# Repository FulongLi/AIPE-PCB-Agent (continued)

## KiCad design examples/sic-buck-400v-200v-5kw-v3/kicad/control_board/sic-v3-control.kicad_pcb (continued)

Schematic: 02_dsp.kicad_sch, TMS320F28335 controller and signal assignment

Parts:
U5: TMS320F28335PGFA; LQFP-176_24x24mm_P0.5mm

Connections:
1V9: U5.4 (VDD), U5.15 (VDD), U5.23 (VDD), U5.29 (VDD), U5.31 (VDD1A18), U5.59 (VDD2A18), U5.61 (VDD), U5.101 (VDD), U5.109 (VDD), U5.117 (VDD), U5.126 (VDD), U5.139 (VDD), U5.146 (VDD), U5.154 (VDD), U5.167 (VDD); also elsewhere on the board
3V3: U5.9 (VDDIO), U5.34 (VDDA2), U5.45 (VDDAIO), U5.71 (VDDIO), U5.84 (VDD3VFL), U5.93 (VDDIO), U5.107 (VDDIO), U5.121 (VDDIO), U5.143 (VDDIO), U5.159 (VDDIO), U5.170 (VDDIO); also elsewhere on the board
ADCREFM: U5.55 (ADCREFM); also elsewhere on the board
ADCREFP: U5.56 (ADCREFP); also elsewhere on the board
ADCRESEXT: U5.57 (ADCRESEXT); also elsewhere on the board
ADC_BUS: U5.42 (ADCINA0); also elsewhere on the board
ADC_CURRENT: U5.41 (ADCINA1); also elsewhere on the board
ADC_IREF: U5.37 (ADCINA5); also elsewhere on the board
ADC_OUT: U5.39 (ADCINA3); also elsewhere on the board
ADC_RAW: U5.40 (ADCINA2); also elsewhere on the board
ADC_TEMP: U5.38 (ADCINA4); also elsewhere on the board
ADC_V12: U5.46 (ADCINB0); also elsewhere on the board
ARMED: U5.21 (GPIO12); also elsewhere on the board
ARM_PULSE: U5.7 (GPIO2); also elsewhere on the board
AUX_OK_N: U5.27 (GPIO16); also elsewhere on the board
BIAS_EN: U5.13 (GPIO6); also elsewhere on the board
BOOT84: U5.169 (GPIO84); also elsewhere on the board
BOOT85: U5.172 (GPIO85); also elsewhere on the board
BOOT86: U5.173 (GPIO86); also elsewhere on the board
BOOT87: U5.174 (GPIO87); also elsewhere on the board
CLK30: U5.105 (XCLKIN); also elsewhere on the board
CURRENT_OK: U5.24 (GPIO13); also elsewhere on the board
DRV_RESET: U5.12 (GPIO5); also elsewhere on the board
EMU0: U5.85 (EMU0); also elsewhere on the board
EMU1: U5.86 (EMU1); also elsewhere on the board
EPWM_A: U5.5 (GPIO0); also elsewhere on the board
EPWM_B: U5.6 (GPIO1); also elsewhere on the board
FAN_TACH: U5.68 (GPIO24); also elsewhere on the board
FLT_H_N: U5.16 (GPIO7); also elsewhere on the board
FLT_L_N: U5.17 (GPIO8); also elsewhere on the board
GND_CTRL: U5.3 (VSS), U5.8 (VSS), U5.14 (VSS), U5.22 (VSS), U5.30 (VSS), U5.32 (VSS1AGND), U5.33 (VSSA2), U5.35 (ADCINA7), U5.36 (ADCINA6), U5.43 (ADCLO), U5.44 (VSSAIO), U5.47 (ADCINB1), U5.48 (ADCINB2), U5.49 (ADCINB3), U5.50 (ADCINB4), U5.51 (ADCINB5), U5.52 (ADCINB6), U5.53 (ADCINB7), U5.54 (ADCREFIN), U5.58 (VSS2AGND), U5.60 (VSS), U5.70 (VSS), U5.83 (VSS), U5.92 (VSS), U5.103 (VSS), U5.104 (X1), U5.106 (VSS), U5.108 (VSS), U5.118 (VSS), U5.120 (VSS), U5.125 (VSS), U5.140 (VSS), U5.144 (VSS), U5.147 (VSS), U5.155 (VSS), U5.160 (VSS), U5.166 (VSS), U5.171 (VSS); also elsewhere on the board
MAIN_CMD: U5.10 (GPIO3); also elsewhere on the board
MAIN_FB: U5.64 (GPIO20); also elsewhere on the board
PG_H_N: U5.28 (GPIO17); also elsewhere on the board
PG_L_N: U5.62 (GPIO18); also elsewhere on the board
PG_S_N: U5.63 (GPIO19); also elsewhere on the board
PRE_CMD: U5.11 (GPIO4); also elsewhere on the board
PRE_FB: U5.65 (GPIO21); also elsewhere on the board
RDY_H: U5.18 (GPIO9); also elsewhere on the board
RDY_L: U5.19 (GPIO10); also elsewhere on the board
RUN_ENABLE: U5.20 (GPIO11); also elsewhere on the board
TCK: U5.87 (TCK); also elsewhere on the board
TDI: U5.76 (TDI); also elsewhere on the board
TDO: U5.77 (TDO); also elsewhere on the board
THERM_OK: U5.26 (GPIO15); also elsewhere on the board
TH_H_PWM: U5.69 (GPIO25); also elsewhere on the board
TH_L_PWM: U5.72 (GPIO26); also elsewhere on the board
TMS: U5.79 (TMS); also elsewhere on the board
TRST: U5.78 (TRST); also elsewhere on the board
UART_RX: U5.141 (GPIO28); also elsewhere on the board
UART_TX: U5.2 (GPIO29); also elsewhere on the board
VOLTAGE_OK: U5.25 (GPIO14); also elsewhere on the board
XRS_N: U5.80 (XRS); also elsewhere on the board

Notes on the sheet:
TMS320F28335 controller and signal assignment
TMS320F28335; ePWM dead-band + asynchronous TZ inputs

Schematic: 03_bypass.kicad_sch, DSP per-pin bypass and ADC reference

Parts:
C17, C18, C19, C20, C21, C22, C23, C24, C25, C26, C27, C28, C29, C30, C31, C32, C33, C34, C35, C36, C37, C38, C39, C40, C41, C42: 100n/50V; C_0603_1608Metric
C43, C44, C45, C46, C47, C48: 2.2u/25V; C_0805_2012Metric
R23: 22k; R_0603_1608Metric

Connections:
1V9: C17.1, C19.1, C20.1, C21.1, C22.1, C25.1, C26.1, C30.1, C32.1, C33.1, C35.1, C36.1, C38.1, C39.1, C41.1, C43.1, C44.1; also elsewhere on the board
3V3: C18.1, C23.1, C24.1, C27.1, C28.1, C29.1, C31.1, C34.1, C37.1, C40.1, C42.1, C45.1, C46.1; also elsewhere on the board
ADCREFM: C47.1; also elsewhere on the board
ADCREFP: C48.1; also elsewhere on the board
ADCRESEXT: R23.1; also elsewhere on the board
GND_CTRL: C17.2, C18.2, C19.2, C20.2, C21.2, C22.2, C23.2, C24.2, C25.2, C26.2, C27.2, C28.2, C29.2, C30.2, C31.2, C32.2, C33.2, C34.2, C35.2, C36.2, C37.2, C38.2, C39.2, C40.2, C41.2, C42.2, C43.2, C44.2, C45.2, C46.2, C47.2, C48.2, R23.2; also elsewhere on the board

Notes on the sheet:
DSP per-pin bypass and ADC reference
Per-pin capacitors; placement tied to actual DSP supply-pad positions

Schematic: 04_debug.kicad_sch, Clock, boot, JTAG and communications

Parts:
C49: 100n/50V; C_0603_1608Metric
J3: TI 14-pin JTAG; pin6 key; PinHeader_2x07_P2.54mm_Vertical
J4: 3.3 V UART; external cable length <=100 mm; PinHeader_1x04_P2.54mm_Vertical
R24: 33; R_0603_1608Metric
R25, R26, R27, R28, R29, R30, R31, R32, R34: 10k; R_0603_1608Metric
R33: 2.2k; R_0603_1608Metric
Y1: ASV-30.000MHZ-EJ-T; Oscillator_SMD_SeikoEpson_SG8002CA-4Pin_7.0x5.0mm

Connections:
3V3: C49.1, J3.5, J4.1, R25.1, R26.1, R27.1, R28.1, R29.1, R30.1, R31.1, R32.1, R34.1, Y1.1 (TRI), Y1.4 (VDD); also elsewhere on the board
BOOT84: R25.2; also elsewhere on the board
BOOT85: R26.2; also elsewhere on the board
BOOT86: R27.2; also elsewhere on the board
BOOT87: R28.2; also elsewhere on the board
CLK30: R24.2; also elsewhere on the board
CLK_SRC: R24.1, Y1.3 (OUT)
EMU0: J3.13, R31.2; also elsewhere on the board
EMU1: J3.14, R32.2; also elsewhere on the board
GND_CTRL: C49.2, J3.4, J3.8, J3.10, J3.12, J4.4, R33.2, Y1.2 (GND); also elsewhere on the board
TCK: J3.9, J3.11; also elsewhere on the board
TDI: J3.3, R30.2; also elsewhere on the board
TDO: J3.7; also elsewhere on the board
TMS: J3.1, R29.2; also elsewhere on the board
TRST: J3.2, R33.1; also elsewhere on the board
UART_RX: J4.3, R34.2; also elsewhere on the board
UART_TX: J4.2; also elsewhere on the board

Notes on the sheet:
Clock, boot, JTAG and communications
30 MHz clock and boot straps
JTAG and 3.3 V UART; accessible control domain only

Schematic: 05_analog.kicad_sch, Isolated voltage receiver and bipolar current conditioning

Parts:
C50, C51, C52, C53, C54, C55, C63, C64: 100p/50V; C_0603_1608Metric
C56, C60, C62, C65, C73: 100n/50V; C_0603_1608Metric
C57, C58, C59, C61: 1u/50V; C_0805_2012Metric
C66, C67, C68, C69, C70, C71, C72: 1n/50V; C_0603_1608Metric
D3, D4, D5, D6, D7, D8, D9, D10, D11, D12, D13, D14, D15, D16: BAT46W-E3-08; D_SOD-123
J5: LEM HO 50-S-0100; JST_PH_B5B-PH-K_1x05_P2.00mm_Vertical
R35, R37, R39, R41, R43, R45, R47, R48, R49, R51, R54, R65: 10k; R_0603_1608Metric
R36, R38, R40, R42, R44, R46: 15k; R_0603_1608Metric
R50, R52: 20k; R_0603_1608Metric
R53: 3.3k; R_0603_1608Metric
R55, R56: 1M; R_0603_1608Metric
R57, R58, R59, R60, R61, R62, R63: 220; R_0603_1608Metric
R64: 43k; R_0603_1608Metric
U6: OPA4192IPWR; TSSOP-14_4.4x5mm_P0.65mm
U7: REF3130AIDBZR; SOT-23
U8: OPA2320AIDGKR; V3_DGK8
U9: LM61CIM3/NOPB; SOT-23

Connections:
3V3: C73.1, D3.1 (K), D5.1 (K), D7.1 (K), D9.1 (K), D11.1 (K), D13.1 (K), D15.1 (K), U9.1 (+VS); also elsewhere on the board
5V: C56.1, C57.1, C58.1, C61.1, C62.1, C65.1, J5.1, U6.4 (V+), U7.1 (IN), U8.8 (V+); also elsewhere on the board
12V_E: R64.1; also elsewhere on the board
ADC_BUS: C66.1, D3.2 (A), D4.1 (K), R57.2; also elsewhere on the board
ADC_CURRENT: C69.1, D9.2 (A), D10.1 (K), R60.2; also elsewhere on the board
ADC_IREF: C70.1, D11.2 (A), D12.1 (K), R61.2; also elsewhere on the board
ADC_OUT: C68.1, D7.2 (A), D8.1 (K), R59.2; also elsewhere on the board
ADC_RAW: C67.1, D5.2 (A), D6.1 (K), R58.2; also elsewhere on the board
ADC_TEMP: C71.1, D13.2 (A), D14.1 (K), R62.2; also elsewhere on the board
ADC_V12: C72.1, D15.2 (A), D16.1 (K), R63.2; also elsewhere on the board
BUS_A: C53.1, R41.2, R42.1, U6.5 (+)
BUS_M: C52.2, R39.2, R40.2, U6.6 (-)
BUS_N: R39.1; also elsewhere on the board
BUS_P: R41.1; also elsewhere on the board
BUS_V: C52.1, R40.1, R57.1, U6.7 (OUTB); also elsewhere on the board
GND_CTRL: C51.2, C53.2, C55.2, C56.2, C57.2, C58.2, C59.2, C60.2, C61.2, C62.2, C65.2, C66.2, C67.2, C68.2, C69.2, C70.2, C71.2, C72.2, C73.2, D4.2 (A), D6.2 (A), D8.2 (A), D10.2 (A), D12.2 (A), D14.2 (A), D16.2 (A), J5.2, R38.2, R42.2, R46.2, R48.2, R54.2, R55.2, R56.2, R65.2, U6.11 (V-), U7.3 (GND), U8.4 (V-), U9.3 (GND); also elsewhere on the board
I_A: C64.1, R51.2, R52.2, U8.5 (+)
I_M: C63.2, R49.2, R50.2, U8.6 (-)
I_OCD_N: R53.2, R54.1; also elsewhere on the board
I_OCD_RAW: J5.5, R53.1
I_RAW: J5.3, R51.1, R55.1
I_REF: J5.4, R56.1, U8.3 (+)
I_REF_BUF: R49.1, R61.1, U8.1 (OUTA), U8.2 (-)
I_V: C63.1, R50.1, R60.1, U8.7 (OUTB); also elsewhere on the board
MID1V5: C64.2, R52.1, U6.13 (-), U6.14 (OUTD)
MID_DIV: C60.1, R47.2, R48.1, U6.12 (+)
OUT_A: C55.1, R45.2, R46.1, U6.10 (+)
OUT_M: C54.2, R43.2, R44.2, U6.9 (-)
OUT_N: R43.1; also elsewhere on the board
OUT_P: R45.1; also elsewhere on the board
OUT_V: C54.1, R44.1, R59.1, U6.8 (OUTC); also elsewhere on the board
RAW_A: C51.1, R37.2, R38.1, U6.3 (+)
RAW_M: C50.2, R35.2, R36.2, U6.2 (-)
RAW_N: R35.1; also elsewhere on the board
RAW_P: R37.1; also elsewhere on the board
RAW_V: C50.1, R36.1, R58.1, U6.1 (OUTA); also elsewhere on the board
REF3: C59.1, R47.1, U7.2 (OUT); also elsewhere on the board
TEMP_V: R62.1, U9.2 (VOUT)
V12_DIV: R63.1, R64.2, R65.1

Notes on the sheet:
Isolated voltage receiver and bipolar current conditioning
Balanced differential voltage receivers; output = 1.5 x differential input
Bipolar current measurement; buffered actual sensor reference
ADC charge reservoirs and input protection

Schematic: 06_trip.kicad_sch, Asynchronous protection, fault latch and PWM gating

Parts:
C74, C75, C76, C77, C78, C79, C80, C81, C82, C83, C84, C85, C86, C87, C88: 100n/50V; C_0603_1608Metric
D17, D18, D19, D20, D21, D22, D23, D24: BAT46W-E3-08; D_SOD-123
R66, R69: 90.9k; R_0603_1608Metric
R67, R68: 9.53k; R_0603_1608Metric
R70: 34k; R_0603_1608Metric
R71, R73, R75: 100k; R_0603_1608Metric
R72: 77k; R_0603_1608Metric
R74: 33.2k; R_0603_1608Metric
R76, R77, R78, R79: 1k; R_0603_1608Metric
R80, R81, R82, R83, R84, R85: 10k; R_0603_1608Metric
R86, R87: 33; R_0603_1608Metric
TP2: TRIPPED; TestPoint_Pad_D1.0mm
TP3: ALL_GOOD; TestPoint_Pad_D1.0mm
U10, U11, U12: TLV3202AIDGKR; V3_DGK8
U13: SN74LV04APWR; TSSOP-14_4.4x5mm_P0.65mm
U14, U15, U16: SN74LV21APWR; TSSOP-14_4.4x5mm_P0.65mm
U17, U19: SN74LVC2G08DCTR; SSOP-8_2.95x2.8mm_P0.65mm
U18: SN74LVC1G74DCTR; SSOP-8_2.95x2.8mm_P0.65mm

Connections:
3V3: C79.1, C80.1, C81.1, C82.1, C83.1, C84.1, C85.1, C86.1, C87.1, C88.1, D17.1 (K), D19.1 (K), D21.1 (K), D23.1 (K), U10.8 (V+), U11.8 (V+), U12.8 (V+), U13.14 (VCC), U14.5 (1D), U14.14 (VCC), U15.14 (VCC), U16.12 (2C), U16.13 (2D), U16.14 (VCC), U17.8 (VCC), U18.2 (D), U18.7 (PRE_N), U18.8 (VCC), U19.8 (VCC); also elsewhere on the board
ALL_GOOD: TP3.1, U17.7 (1Y), U18.6 (CLR_N)
ARMED: U17.5 (2A), U18.5 (Q); also elsewhere on the board
ARM_PULSE: R81.1, U18.1 (CLK); also elsewhere on the board
AUX_OK_N: U15.13 (2D); also elsewhere on the board
BIAS_EN: R85.1; also elsewhere on the board
BIAS_OK: U15.8 (2Y), U16.5 (1D)
BUS_CMP: D19.2 (A), D20.1 (K), R77.2, U11.3 (+), U12.2 (-)
BUS_OV_OK: U12.1 (OUTA), U14.12 (2C)
BUS_V: R77.1; also elsewhere on the board
COIL_INHIBIT: U13.8 (4Y); also elsewhere on the board
CURRENT_OK: U14.6 (1Y), U16.1 (1A); also elsewhere on the board
DRIVERS_OK: U15.6 (1Y), U16.4 (1C)
DRV_RESET: R84.1; also elsewhere on the board
EPWM_A: R82.1, U19.1 (1A); also elsewhere on the board
EPWM_B: R83.1, U19.5 (2A); also elsewhere on the board
FLT_H_N: U15.1 (1A); also elsewhere on the board
FLT_L_N: U15.2 (1B); also elsewhere on the board
GND_CTRL: C74.2, C75.2, C76.2, C77.2, C78.2, C79.2, C80.2, C81.2, C82.2, C83.2, C84.2, C85.2, C86.2, C87.2, C88.2, D18.2 (A), D20.2 (A), D22.2 (A), D24.2 (A), R67.2, R69.2, R71.2, R73.2, R75.2, R80.2, R81.2, R82.2, R83.2, R84.2, R85.2, U10.4 (V-), U11.4 (V-), U12.4 (V-), U13.7 (GND), U13.11 (5A), U13.13 (6A), U14.7 (GND), U15.7 (GND), U16.7 (GND), U17.4 (GND), U18.4 (GND), U19.4 (GND); also elsewhere on the board
I_CMP: D17.2 (A), D18.1 (K), R76.2, U10.3 (+), U10.6 (-)
I_HI: C75.1, R68.2, R69.1, U10.5 (+)
I_HIGH_OK: U10.7 (OUTB), U14.2 (1B)
I_LO: C74.1, R66.2, R67.1, U10.2 (-)
I_LOW_OK: U10.1 (OUTA), U14.1 (1A)
I_OCD_N: U14.4 (1C); also elsewhere on the board
I_V: R76.1; also elsewhere on the board
OUT_CMP: D23.2 (A), D24.1 (K), R79.2, U11.6 (-)
OUT_V: R79.1; also elsewhere on the board
PG_H_N: U13.1 (1A); also elsewhere on the board
PG_H_OK: U13.2 (1Y), U15.9 (2A)
PG_L_N: U13.3 (2A); also elsewhere on the board
PG_L_OK: U13.4 (2Y), U15.10 (2B)
PG_S_N: U13.5 (3A); also elsewhere on the board
PG_S_OK: U13.6 (3Y), U15.12 (2C)
PWM_ENABLE: U17.3 (2Y), U19.2 (1B), U19.6 (2B)
PWM_H: R86.2; also elsewhere on the board
PWM_H_SRC: R86.1, U19.7 (1Y)
PWM_L: R87.2; also elsewhere on the board
PWM_L_SRC: R87.1, U19.3 (2Y)
RAW_CMP: D21.2 (A), D22.1 (K), R78.2, U12.6 (-)
RAW_OV_OK: U12.7 (OUTB), U14.13 (2D)
RAW_V: R78.1; also elsewhere on the board
RDY_H: U15.4 (1C); also elsewhere on the board
RDY_L: U15.5 (1D); also elsewhere on the board
REF3: R66.1, R68.1, R70.1, R72.1, R74.1; also elsewhere on the board
RUN_ENABLE: R80.1, U17.6 (2B); also elsewhere on the board
STAGE_OK: U16.6 (1Y), U17.1 (1A)
SYSTEM_OK: U13.9 (4A), U16.8 (2Y), U17.2 (1B)
THERM_OK: U16.9 (2A); also elsewhere on the board
TRIPPED: TP2.1, U18.3 (Q_N)
VOLTAGE_OK: U14.8 (2Y), U16.2 (1B); also elsewhere on the board
V_BUSOV: C78.1, R74.2, R75.1, U12.3 (+), U12.5 (+)
V_HIGH_OK: U11.7 (OUTB), U14.10 (2B)
V_LOW_OK: U11.1 (OUTA), U14.9 (2A)
V_OV: C76.1, R70.2, R71.1, U11.5 (+)
V_UV: C77.1, R72.2, R73.1, U11.2 (-)
XRS_N: U16.10 (2B); also elsewhere on the board

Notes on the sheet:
Asynchronous protection, fault latch and PWM gating
Hardware current window ±38 A, OVP225 V and UVLO340 V
Power-good polarity, asynchronous fault tree and latched inhibit

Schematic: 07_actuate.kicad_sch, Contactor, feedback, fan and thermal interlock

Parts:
C89: 100u/25V; CP_Elec_8x10.5
C90: 100n/50V; C_0603_1608Metric
C91, C92: 10n/50V; C_0603_1608Metric
D25, D26: SSC54-E3/57T; D_SMC
J6: 12 V COIL / FAN; TerminalBlock_Phoenix_MKDS-1,5-2-5.08_1x02_P5.08mm_Horizont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
J7: MAIN COIL; TerminalBlock_Phoenix_MKDS-1,5-2-5.08_1x02_P5.08mm_Horizont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
J8: PRE COIL; TerminalBlock_Phoenix_MKDS-1,5-2-5.08_1x02_P5.08mm_Horizont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
J9: MAIN AUX CONTACT; PinHeader_1x02_P2.54mm_Vertical
J10: PRE AUX CONTACT; PinHeader_1x02_P2.54mm_Vertical
J11: Series NC90C sink thermostat + NC110C choke therm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; PinHeader_1x02_P2.54mm_Vertical
J12: 12V fan; open-collector tach; fan failure checked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; PinHeader_1x03_P2.54mm_Vertical
Q2, Q3: IRLZ44NPBF; TO-220-3_Vertical
R88, R90: 100; R_0603_1608Metric
R89, R91, R92, R93, R97, R101: 10k; R_0603_1608Metric
R94, R95, R98, R99: 200; R_2512_6332Metric
R96, R100: 33k; R_0603_1608Metric
R102: 1k; R_0603_1608Metric
R103: 4.7k; R_0603_1608Metric
U20: SN74AHCT125PWR; TSSOP-14_4.4x5mm_P0.65mm

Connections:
3V3: J11.1, R103.1; also elsewhere on the board
5V: C90.1, U20.10 (3OE_N), U20.13 (4OE_N), U20.14 (VCC); also elsewhere on the board
12V_COIL: C89.1, D25.1 (K), D26.1 (K), J6.1, J7.1, J8.1, J9.1, J10.1, J12.2
COIL_INHIBIT: U20.1 (1OE_N), U20.4 (2OE_N); also elsewhere on the board
FAN_TACH: J12.3, R103.2; also elsewhere on the board
GND_CTRL: C89.2, C90.2, C91.2, C92.2, J6.2, J12.1, Q2.3 (S), Q3.3 (S), R89.2, R91.2, R92.2, R93.2, R94.2, R95.2, R97.2, R98.2, R99.2, R101.2, R102.2, U20.7 (GND), U20.9 (3A), U20.12 (4A); also elsewhere on the board
MAIN_AUX: J9.2, R94.1, R95.1, R96.1
MAIN_CMD: R92.1, U20.2 (1A); also elsewhere on the board
MAIN_DRIVE: R88.1, U20.3 (1Y)
MAIN_FB: C91.1, R96.2, R97.1; also elsewhere on the board
MAIN_G: Q2.1 (G), R88.2, R89.1
MAIN_LOW: D25.2 (A), J7.2, Q2.2 (D)
PRE_AUX: J10.2, R98.1, R99.1, R100.1
PRE_CMD: R93.1, U20.5 (2A); also elsewhere on the board
PRE_DRIVE: R90.1, U20.6 (2Y)
PRE_FB: C92.1, R100.2, R101.1; also elsewhere on the board
PRE_G: Q3.1 (G), R90.2, R91.1
PRE_LOW: D26.2 (A), J8.2, Q3.2 (D)
THERM_OK: J11.2, R102.1; also elsewhere on the board

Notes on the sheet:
Contactor, feedback, fan and thermal interlock
Dedicated 12 V coil/fan branch; external 8 A fuse and return
Main and precharge drivers; fail-safe default off
Contactor auxiliary contacts with manufacturer minimum wetting current
Fail-open thermal / emergency-stop loop and fan tachometer

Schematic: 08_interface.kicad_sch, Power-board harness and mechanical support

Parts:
H1, H2, H3, H4: M3 insulated standoff; MountingHole_3.2mm_M3
J13: POWER / CONTROL — 40-way; IDC-Header_2x20_P2.54mm_Vertical

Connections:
3V3: J13.37, J13.38; also elsewhere on the board
12V_E: J13.33, J13.34; also elsewhere on the board
BIAS_EN: J13.8; also elsewhere on the board
BUS_N: J13.26; also elsewhere on the board
BUS_P: J13.25; also elsewhere on the board
DRV_RESET: J13.6; also elsewhere on the board
FLT_H_N: J13.10; also elsewhere on the board
FLT_L_N: J13.12; also elsewhere on the board
GND_CTRL: J13.1, J13.3, J13.5, J13.7, J13.9, J13.11, J13.13, J13.15, J13.17, J13.19, J13.21, J13.29, J13.31, J13.35, J13.36, J13.39, J13.40; also elsewhere on the board
OUT_N: J13.28; also elsewhere on the board
OUT_P: J13.27; also elsewhere on the board
PG_H_N: J13.18; also elsewhere on the board
PG_L_N: J13.20; also elsewhere on the board
PG_S_N: J13.22; also elsewhere on the board
PWM_H: J13.2; also elsewhere on the board
PWM_L: J13.4; also elsewhere on the board
RAW_N: J13.24; also elsewhere on the board
RAW_P: J13.23; also elsewhere on the board
RDY_H: J13.14; also elsewhere on the board
RDY_L: J13.16; also elsewhere on the board
TH_H_PWM: J13.30; also elsewhere on the board
TH_L_PWM: J13.32; also elsewhere on the board

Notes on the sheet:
Power-board harness and mechanical support
Keyed SELV harness to the power board
Mechanical

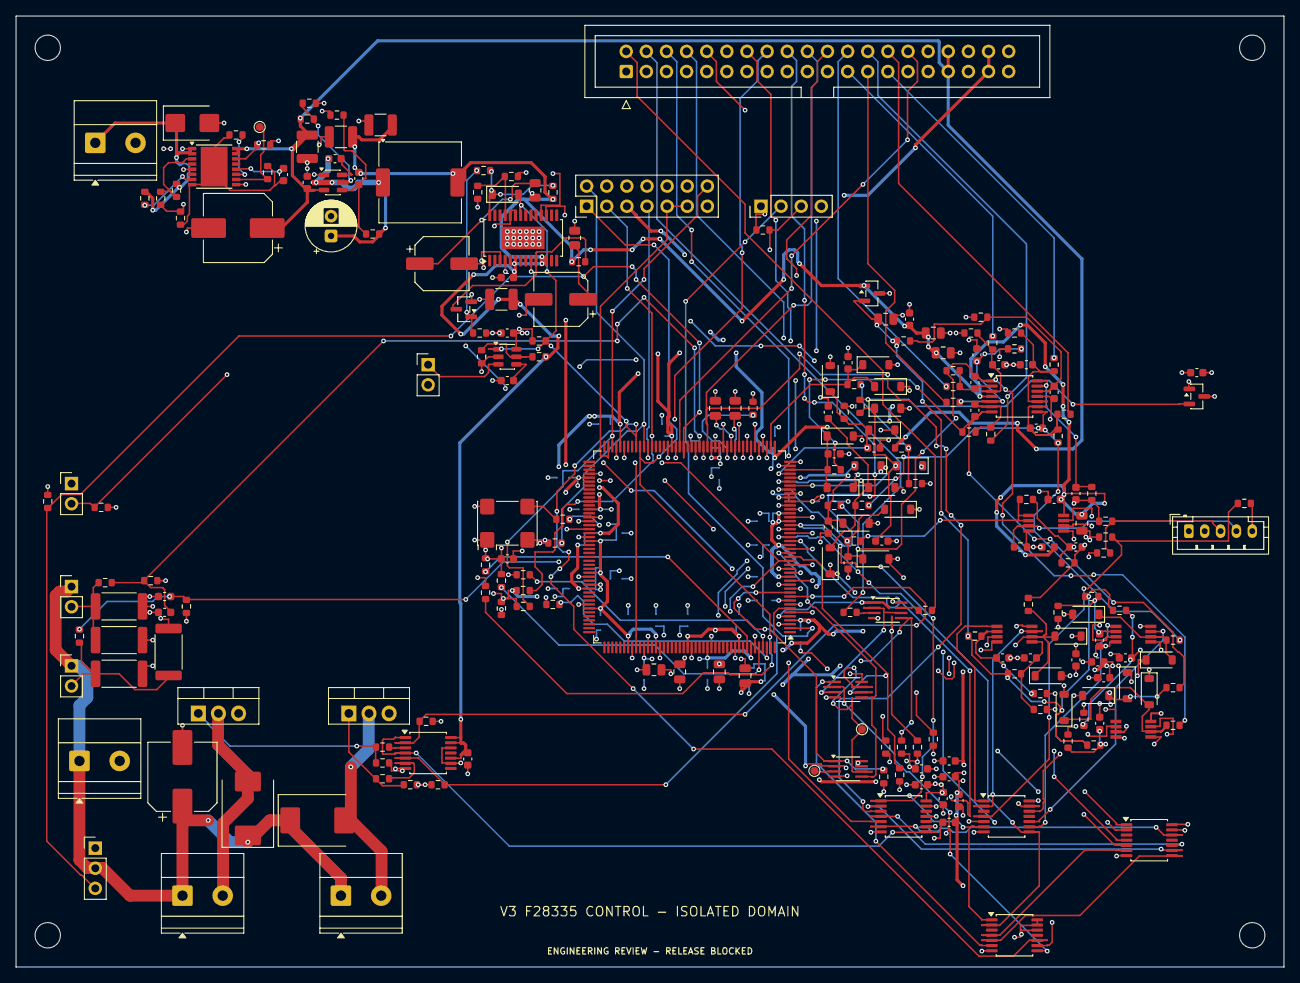
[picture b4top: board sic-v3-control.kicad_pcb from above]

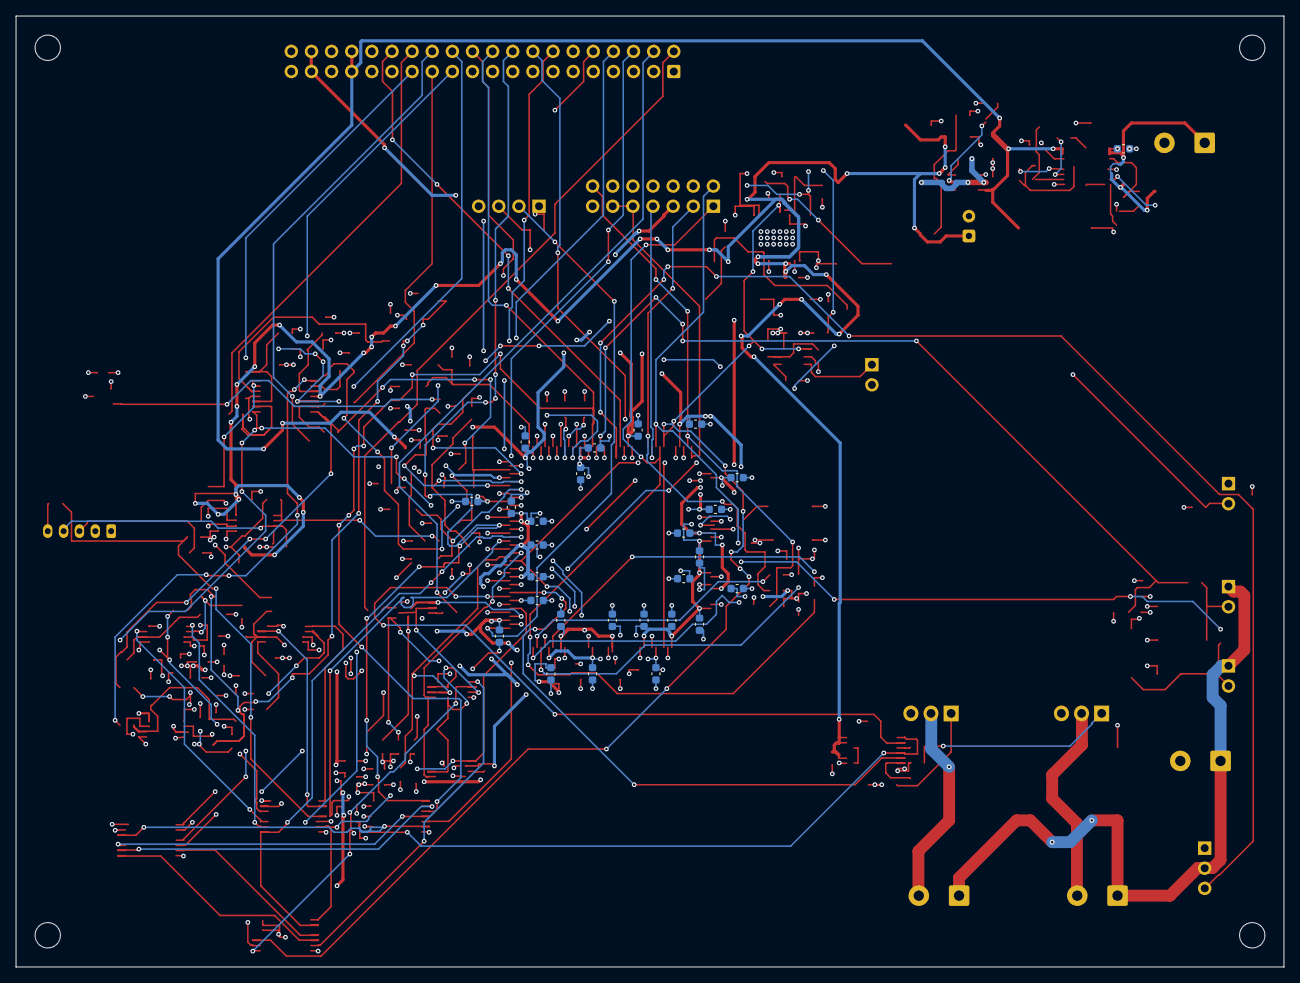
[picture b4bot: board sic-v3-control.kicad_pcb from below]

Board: 4 copper layers, 160.0 x 120.0 mm, 266 parts (27 on the bottom side), 144 nets.

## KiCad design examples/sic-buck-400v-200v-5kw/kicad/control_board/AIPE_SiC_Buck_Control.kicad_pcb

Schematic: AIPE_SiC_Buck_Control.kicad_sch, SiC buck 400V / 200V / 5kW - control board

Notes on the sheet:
AI-GENERATED ENGINEERING PROTOTYPE - V2.2 - HUMAN REVIEW REQUIRED
Design basis: examples/sic-buck-400v-200v-5kw/design/design_decisions.json (schema 3, 2026-10-10) - single source of truth; electrical model automation/kicad_tools/sic_buck_control_model.py; generator automation/kicad_tools/generate_sic_schematics.py. 400 V (360-440 V) to 200 V / 25 A / 5 kW / 50 k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

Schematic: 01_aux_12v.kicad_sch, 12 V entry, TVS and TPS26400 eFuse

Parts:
C1, C2: 100n/50V; C_0603_1608Metric
C3: 100u/25V; CP_Elec_8x10.5
D1: SMBJ15CA; D_SMB
J1: 12 V in; TerminalBlock_Phoenix_MKDS-1,5-2-5.08_1x02_P5.08mm_Horizont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
R1: 107k; R_0603_1608Metric
R2: 4.42k; R_0603_1608Metric
R3, R7: 10k; R_0603_1608Metric
R4: 6.04k; R_0603_1608Metric
R5: 14.7k; R_0603_1608Metric
R6: 100k; R_0603_1608Metric
R8: 150k; R_0603_1608Metric
R9: 33.2k; R_0603_1608Metric
U1: TPS26400PWPR; HTSSOP-16-1EP_4.4x5mm_P0.65mm_EP3.4x5mm

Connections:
3V3: R7.1; also elsewhere on the board
12V_IN: C1.1, D1.1 (A1), J1.1, R1.1, R6.1, U1.1 (IN), U1.2 (IN)
12V_PROT: C3.1, R8.1, U1.15 (OUT), U1.16 (OUT); also elsewhere on the board
EFUSE_DVDT: C2.1, U1.12 (dVdT)
EFUSE_ILIM: R4.1, U1.11 (ILIM)
EFUSE_OVP: R2.2, R3.1, U1.5 (OVP)
EFUSE_RTN: C2.2, R3.2, R4.2, R5.2, U1.8 (RTN), U1.17 (PAD)
EFUSE_SHDN: R6.2, U1.7 (SHDN)
EFUSE_UVLO: R1.2, R2.1, U1.3 (UVLO)
FLT_12V_N: R7.2, U1.14 (FLT); also elsewhere on the board
GND_CTRL: C1.2, C3.2, D1.2 (A2), J1.2, R9.2, U1.9 (GND); also elsewhere on the board
I12V_MON: R5.1, U1.10 (IMON); also elsewhere on the board
V12V_MON: R8.2, R9.1; also elsewhere on the board

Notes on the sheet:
12 V entry, TVS and TPS26400 eFuse
TPS26400 eFuse: UVLO 10.0 / 9.3 V and OVP 14.45 / 13.4 V from 107 k / 4.42 k / 10.0 k, R_ILIM 6.04 k (I_CB about 1.96 A), C_dVdT 100 nF, R_IMON 14.7 k, MODE open = circuit breaker (CR-18). RTN (EFUSE_RTN) is never tied to GND_CTRL (A-C3). PWR_FLAG symbols state supply provenance for ERC; they do no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
Supply provenance (PWR_FLAG)

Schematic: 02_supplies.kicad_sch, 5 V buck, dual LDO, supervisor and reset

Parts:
C4: 10u/25V; C_1210_3225Metric
C5, C6, C13, C16, C76: 100n/50V; C_0603_1608Metric
C7, C8, C14: 22u/25V; C_1210_3225Metric
C9: 220u/16V; CP_Radial_D6.3mm_P2.50mm
C10: 56p/50V; C_0603_1608Metric
C11, C12: 100u/6.3V; CP_Elec_6.3x5.9
C15: 10n/50V; C_0603_1608Metric
D2: BAT54,215; SOT-23
J2: J_RESET: manual reset through the supervisor MR p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; PinHeader_1x02_P2.54mm_Vertical
L1: 10uH; L_Coilcraft_MSS1048-XXX
Q1: MMBT3904,215; SOT-23
R10, R12, R19: 100k; R_0603_1608Metric
R11: 20k; R_0603_1608Metric
R13: 13.3k; R_0603_1608Metric
R14: 18.2k; R_0603_1608Metric
R15: 30.1k; R_0603_1608Metric
R16, R17, R18, R23, R24: 10k; R_0603_1608Metric
R20, R21: 0.1; R_0805_2012Metric
R22: 101k; R_0603_1608Metric
U2: TPS54302DDCR; SOT-23-6
U3: TPS767D301PWPR; HTSSOP-28-1EP_4.4x9.7mm_P0.65mm_EP2.85x5.4mm
U4: TPS3808G01DBVR; SOT-23-6

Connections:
1V9: R14.1, R20.1, U3.23 (1OUT), U3.24 (1OUT); also elsewhere on the board
1V9_BULK: C11.1, R20.2
3V3: C16.1, C76.1, R21.1, R24.1, U3.17 (2OUT), U3.18 (2OUT), U4.6 (VDD); also elsewhere on the board
3V3_BULK: C12.1, R21.2
5V: C7.1, C8.1, C9.1, C10.1, C13.1, C14.1, L1.2, R12.1, R16.1, R17.1, R22.1, U3.5 (1IN), U3.6 (1IN), U3.11 (2IN), U3.12 (2IN); also elsewhere on the board
5V_BST: C6.1, U2.6 (BOOT)
5V_EN: R10.2, R11.1, U2.5 (EN)
5V_FB: C10.2, R12.2, R13.1, U2.4 (FB)
5V_SW: C6.2, L1.1, U2.2 (SW)
12V_PROT: C4.1, C5.1, R10.1, U2.3 (VIN); also elsewhere on the board
CORE_OK: D2.3 (K), R16.2, R18.1, U3.28 (1RESET_N)
FB19: R14.2, R15.1, U3.25 (1FB)
GND_CTRL: C4.2, C5.2, C7.2, C8.2, C9.2, C11.2, C12.2, C13.2, C14.2, C15.2, C16.2, C76.2, J2.2, Q1.2 (E), R11.2, R13.2, R15.2, R19.2, R23.2, U2.1 (GND), U3.3 (1GND), U3.4 (1EN_N), U3.9 (2GND), U3.29 (EP), U4.2 (GND); also elsewhere on the board
IO_EN_N: Q1.3 (C), R17.2, U3.10 (2EN_N)
MON5: R22.2, R23.1, U4.5 (SENSE)
MR_N: J2.1, U4.3 (MR_N)
RESET_CT: C15.1, U4.4 (CT)
SEQ_BASE: Q1.1 (B), R18.2, R19.1
XRS_N: D2.1 (A), R24.2, U3.22 (2RESET_N), U4.1 (RESET_N); also elsewhere on the board

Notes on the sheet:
5 V buck, dual LDO, supervisor and reset
TPS54302 5 V buck (FB 100 k / 13.3 k), TPS767D301 dual LDO with core-first sequencing (1.9 V from 18.2 k / 30.1 k, 3.3 V fixed), TPS3808G01 supervisor 101 k / 10 k (4.50 V threshold, CT 10 nF). The -EP LDO variant is NRND; TLV752 is the named alternative.
TPS54302 5 V buck
TPS767D301 dual LDO, core-first sequencing
TPS3808 5 V supervisor and reset
U4 dedicated local bypass (V2.2)
Supply provenance (PWR_FLAG)

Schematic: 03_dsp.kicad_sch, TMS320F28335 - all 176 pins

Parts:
U5: TMS320F28335PGFA; LQFP-176_24x24mm_P0.5mm

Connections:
1V9: U5.4 (VDD), U5.15 (VDD), U5.23 (VDD), U5.29 (VDD), U5.31 (VDD1A18), U5.59 (VDD2A18), U5.61 (VDD), U5.101 (VDD), U5.109 (VDD), U5.117 (VDD), U5.126 (VDD), U5.139 (VDD), U5.146 (VDD), U5.154 (VDD), U5.167 (VDD); also elsewhere on the board
3V3: U5.9 (VDDIO), U5.34 (VDDA2), U5.45 (VDDAIO), U5.71 (VDDIO), U5.84 (VDD3VFL), U5.93 (VDDIO), U5.107 (VDDIO), U5.121 (VDDIO), U5.143 (VDDIO), U5.159 (VDDIO), U5.170 (VDDIO); also elsewhere on the board
ADCREFM: U5.55 (ADCREFM); also elsewhere on the board
ADCREFP: U5.56 (ADCREFP); also elsewhere on the board
ADCRESEXT: U5.57 (ADCRESEXT); also elsewhere on the board
ADC_I12V: U5.46 (ADCINB0); also elsewhere on the board
ADC_ISENSE: U5.41 (ADCINA1); also elsewhere on the board
ADC_ISENSE_REF: U5.38 (ADCINA4); also elsewhere on the board
ADC_TEMP_CTRL: U5.39 (ADCINA3); also elsewhere on the board
ADC_TEMP_HS: U5.40 (ADCINA2); also elsewhere on the board
ADC_V12V: U5.49 (ADCINB3); also elsewhere on the board
ADC_VIN: U5.42 (ADCINA0); also elsewhere on the board
ADC_VOUT: U5.47 (ADCINB1); also elsewhere on the board
ARM: U5.7 (GPIO2); also elsewhere on the board
BIAS_EN: U5.12 (GPIO5); also elsewhere on the board
BOOT84: U5.169 (GPIO84); also elsewhere on the board
BOOT85: U5.172 (GPIO85); also elsewhere on the board
BOOT86: U5.173 (GPIO86); also elsewhere on the board
BOOT87: U5.174 (GPIO87); also elsewhere on the board
CLK30: U5.105 (XCLKIN); also elsewhere on the board
DSP_TRIP_N: U5.13 (GPIO6); also elsewhere on the board
EMU0: U5.85 (EMU0); also elsewhere on the board
EMU1: U5.86 (EMU1); also elsewhere on the board
EPWM1A: U5.5 (GPIO0); also elsewhere on the board
EPWM1B: U5.6 (GPIO1); also elsewhere on the board
ESTOP_N: U5.63 (GPIO19); also elsewhere on the board
FAN_TACH: U5.68 (GPIO24); also elsewhere on the board
FAULT_N: U5.21 (GPIO12); also elsewhere on the board
FLT_12V_N: U5.27 (GPIO16); also elsewhere on the board
FLT_H_N: U5.16 (GPIO7); also elsewhere on the board
FLT_L_N: U5.17 (GPIO8); also elsewhere on the board
GND_CTRL: U5.3 (VSS), U5.8 (VSS), U5.14 (VSS), U5.22 (VSS), U5.30 (VSS), U5.32 (VSS1AGND), U5.33 (VSSA2), U5.35 (ADCINA7), U5.36 (ADCINA6), U5.37 (ADCINA5), U5.43 (ADCLO), U5.44 (VSSAIO), U5.48 (ADCINB2), U5.50 (ADCINB4), U5.51 (ADCINB5), U5.52 (ADCINB6), U5.53 (ADCINB7), U5.54 (ADCREFIN), U5.58 (VSS2AGND), U5.60 (VSS), U5.70 (VSS), U5.83 (VSS), U5.92 (VSS), U5.103 (VSS), U5.104 (X1), U5.106 (VSS), U5.108 (VSS), U5.118 (VSS), U5.120 (VSS), U5.125 (VSS), U5.140 (VSS), U5.144 (VSS), U5.147 (VSS), U5.155 (VSS), U5.160 (VSS), U5.166 (VSS), U5.171 (VSS); also elsewhere on the board
LED_FAULT: U5.66 (GPIO22); also elsewhere on the board
LED_RUN: U5.65 (GPIO21); also elsewhere on the board
OC_N: U5.24 (GPIO13); also elsewhere on the board
OTP_N: U5.26 (GPIO15); also elsewhere on the board
OVP_N: U5.20 (GPIO11); also elsewhere on the board
PG_BIAS_H_N: U5.28 (GPIO17); also elsewhere on the board
PG_BIAS_L_N: U5.62 (GPIO18); also elsewhere on the board
PG_BIAS_S_N: U5.64 (GPIO20); also elsewhere on the board
RDY_H: U5.18 (GPIO9); also elsewhere on the board
RDY_L: U5.19 (GPIO10); also elsewhere on the board
RELAY_ON: U5.10 (GPIO3); also elsewhere on the board
RESET_N: U5.11 (GPIO4); also elsewhere on the board
SPARE_D1: U5.72 (GPIO26); also elsewhere on the board
SPARE_D2: U5.73 (GPIO27); also elsewhere on the board
TCK: U5.87 (TCK); also elsewhere on the board
TDI: U5.76 (TDI); also elsewhere on the board
TDO: U5.77 (TDO); also elsewhere on the board
TMS: U5.79 (TMS); also elsewhere on the board
TRST: U5.78 (TRST); also elsewhere on the board
UART_RX: U5.141 (GPIO28); also elsewhere on the board
UART_TX: U5.2 (GPIO29); also elsewhere on the board
UVLO_N: U5.25 (GPIO14); also elsewhere on the board
XRS_N: U5.80 (XRS); also elsewhere on the board

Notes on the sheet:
TMS320F28335 - all 176 pins
TMS320F28335PGFA, all 176 pins; units split into supplies, ADC, connected GPIO and unused pins. Pin map per design_decisions.json.
TMS320F28335PGFA

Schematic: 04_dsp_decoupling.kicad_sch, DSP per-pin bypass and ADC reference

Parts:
C17, C18, C19, C20, C21, C22, C23, C24, C25, C26, C27, C28, C29, C30, C31, C32, C33, C34, C35, C36, C37, C38, C39, C40, C41, C42: 100n/50V; C_0603_1608Metric
C43, C44, C45, C46, C47, C48: 2.2u/25V; C_0805_2012Metric
R25: 22k; R_0603_1608Metric

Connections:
1V9: C17.1, C19.1, C20.1, C21.1, C22.1, C25.1, C26.1, C30.1, C32.1, C33.1, C35.1, C36.1, C38.1, C39.1, C41.1, C43.1, C44.1; also elsewhere on the board
3V3: C18.1, C23.1, C24.1, C27.1, C28.1, C29.1, C31.1, C34.1, C37.1, C40.1, C42.1, C45.1, C46.1; also elsewhere on the board
ADCREFM: C47.1; also elsewhere on the board
ADCREFP: C48.1; also elsewhere on the board
ADCRESEXT: R25.1; also elsewhere on the board
GND_CTRL: C17.2, C18.2, C19.2, C20.2, C21.2, C22.2, C23.2, C24.2, C25.2, C26.2, C27.2, C28.2, C29.2, C30.2, C31.2, C32.2, C33.2, C34.2, C35.2, C36.2, C37.2, C38.2, C39.2, C40.2, C41.2, C42.2, C43.2, C44.2, C45.2, C46.2, C47.2, C48.2, R25.2; also elsewhere on the board

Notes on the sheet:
DSP per-pin bypass and ADC reference
One 100 nF per DSP supply pin (26), 2 x 2.2 uF per rail, 2.2 uF on ADCREFP/ADCREFM, 22 k on ADCRESEXT (SPRS439Q).

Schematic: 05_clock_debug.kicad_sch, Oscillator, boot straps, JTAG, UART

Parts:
C49: 100n/50V; C_0603_1608Metric
J3: J_JTAG: TI 14-pin, key pin 6 absent; TCK_RET tied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; PinHeader_2x07_P2.54mm_Vertical
J4: J_BOOT: jumper 1-2 = SCI-A boot, 2-3 or open = fl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; PinHeader_1x03_P2.54mm_Vertical
J5: J_UART: SCI-A, 3.3 V levels only; PinHeader_1x03_P2.54mm_Vertical
R26: 33; R_0603_1608Metric
R27, R28, R29, R30, R31, R32, R33, R34: 4.7k; R_0603_1608Metric
R35: 2.2k; R_0603_1608Metric
R36, R37: 10k; R_0603_1608Metric
Y1: ASV-30.000MHZ-EJ-T; Oscillator_SMD_SeikoEpson_SG8002CA-4Pin_7.0x5.0mm

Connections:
3V3: C49.1, J3.5, J4.3, R27.1, R28.1, R29.1, R30.1, R31.1, R32.1, R33.1, R34.1, R37.1, Y1.1 (TRI), Y1.4 (VDD); also elsewhere on the board
BOOT84: J4.2, R27.2; also elsewhere on the board
BOOT85: R28.2; also elsewhere on the board
BOOT86: R29.2; also elsewhere on the board
BOOT87: R30.2; also elsewhere on the board
CLK30: R26.2; also elsewhere on the board
CLK30_SOURCE: R26.1, Y1.3 (OUT)
EMU0: J3.13, R31.2; also elsewhere on the board
EMU1: J3.14, R32.2; also elsewhere on the board
GND_CTRL: C49.2, J3.4, J3.8, J3.10, J3.12, J4.1, J5.3, R35.2, R36.2, Y1.2 (GND); also elsewhere on the board
TCK: J3.9, J3.11, R36.1; also elsewhere on the board
TDI: J3.3, R34.2; also elsewhere on the board
TDO: J3.7; also elsewhere on the board
TMS: J3.1, R33.2; also elsewhere on the board
TRST: J3.2, R35.1; also elsewhere on the board
UART_RX: J5.2, R37.2; also elsewhere on the board
UART_TX: J5.1; also elsewhere on the board

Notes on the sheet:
Oscillator, boot straps, JTAG, UART
30 MHz oscillator on XCLKIN (X1 grounded, X2 open), 33 ohm series; boot straps GPIO84-87 pulled high; TI 14-pin JTAG; SCI-A header.
30 MHz oscillator
Boot straps and JTAG
SCI-A UART header

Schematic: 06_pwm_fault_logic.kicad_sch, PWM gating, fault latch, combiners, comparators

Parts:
C50, C51: 1u/50V; C_0805_2012Metric
C52, C53, C55, C56, C57, C58, C59, C60, C61, C62, C77, C78, C79: 100n/50V; C_0603_1608Metric
C54: 100n/50V; C_0603_1608Metric; not fitted
J6: J_ESTOP: normally-closed E-stop loop between 3V3 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; PinHeader_1x02_P2.54mm_Vertical
R38, R39: 33; R_0603_1608Metric
R40, R41, R42, R43, R44, R45, R46, R47, R48, R49, R50, R51, R52, R56, R60, R61, R62, R63: 10k; R_0603_1608Metric
R53, R57: 1k; R_0603_1608Metric
R54: 11k; R_0603_1608Metric
R55: 953; R_0603_1608Metric
R58: 1.91k; R_0603_1608Metric
R59: 21.5k; R_0603_1608Metric
U6: SN74LVC2G08DCTR; SSOP-8_2.95x2.8mm_P0.65mm
U7: SN74LVC1G74DCTR; SSOP-8_2.95x2.8mm_P0.65mm
U8, U9, U10: SN74LV21APWR; TSSOP-14_4.4x5mm_P0.65mm
U11: SN74LV04APWR; TSSOP-14_4.4x5mm_P0.65mm
U12: REF3125AIDBZR; SOT-23
U13, U14: TLV1702AIDGKR; VSSOP-8_3x3mm_P0.65mm

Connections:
3V3: C50.1, C55.1, C56.1, C57.1, C58.1, C59.1, C60.1, C61.1, C62.1, C77.1, C78.1, C79.1, J6.1, R43.1, R44.1, R45.1, R46.1, R47.1, R48.1, R49.1, R50.1, R51.1, R60.1, R61.1, R62.1, R63.1, U6.8 (VCC), U7.2 (D), U7.7 (PRE_N), U7.8 (VCC), U8.14 (VCC), U9.14 (VCC), U10.12 (2C), U10.13 (2D), U10.14 (VCC), U11.14 (VCC), U12.1 (IN), U13.8 (V+), U14.8 (V+); also elsewhere on the board
ARM: R42.1, U7.1 (CLK); also elsewhere on the board
DSP_TRIP_N: R51.2, U9.2 (1B); also elsewhere on the board
EPWM1A: R40.1, U6.1 (1A); also elsewhere on the board
EPWM1B: R41.1, U6.5 (2A); also elsewhere on the board
ESTOP_N: J6.2, R52.1, U9.1 (1A); also elsewhere on the board
FAULT_LATCH_N: U7.6 (CLR_N), U9.8 (2Y); also elsewhere on the board
FAULT_N: U7.5 (Q), U10.5 (1D); also elsewhere on the board
FLT_12V_N: U8.12 (2C); also elsewhere on the board
FLT_H_N: R43.2, U8.1 (1A); also elsewhere on the board
FLT_L_N: R44.2, U8.2 (1B); also elsewhere on the board
G1_N: U8.6 (1Y), U9.9 (2A)
G2_N: U8.8 (2Y), U9.10 (2B)
G3_N: U9.6 (1Y), U9.12 (2C)
GATE_EN: U6.2 (1B), U6.6 (2B), U10.6 (1Y); also elsewhere on the board
GND_CTRL: C50.2, C51.2, C52.2, C53.2, C54.2, C55.2, C56.2, C57.2, C58.2, C59.2, C60.2, C61.2, C62.2, C77.2, C78.2, C79.2, R40.2, R41.2, R42.2, R52.2, R54.2, R56.2, R58.2, U6.4 (GND), U7.4 (GND), U8.7 (GND), U9.7 (GND), U10.7 (GND), U11.7 (GND), U11.11 (5A), U11.13 (6A), U12.3 (GND), U13.4 (V-), U14.4 (V-); also elsewhere on the board
OC_N: R47.2, U8.4 (1C); also elsewhere on the board
OTP_N: R63.2, U8.10 (2B), U14.7 (2OUT); also elsewhere on the board
OTP_REF: U14.6 (2IN-); also elsewhere on the board
OVP_IN_N: R60.2, U8.5 (1D), U10.9 (2A), U13.1 (1OUT)
OVP_IN_REF: C52.1, R53.2, R54.1, U13.3 (1IN+)
OVP_N: U10.8 (2Y); also elsewhere on the board
OVP_OUT_N: R61.2, U8.9 (2A), U10.10 (2B), U13.7 (2OUT)
OVP_OUT_REF: C53.1, R55.2, R56.1, U13.5 (2IN+)
PG_BIAS_H_N: R48.2, U11.3 (2A); also elsewhere on the board
PG_BIAS_H_OK: U9.4 (1C), U11.4 (2Y)
PG_BIAS_L_N: R49.2, U11.5 (3A); also elsewhere on the board
PG_BIAS_L_OK: U9.5 (1D), U11.6 (3Y)
PG_BIAS_S_N: R50.2, U11.9 (4A); also elsewhere on the board
PG_BIAS_S_OK: U9.13 (2D), U11.8 (4Y)
PWM_H: R38.2; also elsewhere on the board
PWM_H_G: R38.1, U6.7 (1Y)
PWM_L: R39.2; also elsewhere on the board
PWM_L_G: R39.1, U6.3 (2Y)
RDY_H: R45.2, U10.2 (1B); also elsewhere on the board
RDY_L: R46.2, U10.4 (1C); also elsewhere on the board
REF2V5: C51.1, R53.1, R55.1, R57.1, U12.2 (OUT)
TEMP_HS_NTC: U14.5 (2IN+); also elsewhere on the board
UVLO: R59.1, R62.2, U11.1 (1A), U14.1 (1OUT)
UVLO_N: U10.1 (1A), U11.2 (1Y); also elsewhere on the board
UVLO_REF: C54.1, R57.2, R58.1, R59.2, U14.3 (1IN+)
VIN_SENSE: U13.2 (1IN-), U14.2 (1IN-); also elsewhere on the board
VOUT_SENSE: U13.6 (2IN-); also elsewhere on the board
XRS_N: U8.13 (2D); also elsewhere on the board

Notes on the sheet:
PWM gating, fault latch, combiners, comparators
ePWM1A/1B AND GATE_EN (SN74LVC2G08) -> 33 ohm -> mezzanine; SN74LVC1G74 fault latch (D = 1, CLK = ARM, CLR_N = FAULT_LATCH_N, Q = FAULT_N = ARMED); 3 x SN74LV21A combiners; SN74LV04A restores the UVLO and PG_BIAS polarities (A-C6, A-C7); TLV1702 comparators with REF3125-derived thresholds.
PWM gating (SN74LVC2G08)
Fault latch (SN74LVC1G74)
Fault combiners, polarity restoration, pull-ups, E-stop
REF3125 reference and OVP / UVLO thresholds
TLV1702 comparators
Logic supply bypass
U8 dedicated local bypass (V2.2)
U10 dedicated local bypass (V2.2)
U11 dedicated local bypass (V2.2)
